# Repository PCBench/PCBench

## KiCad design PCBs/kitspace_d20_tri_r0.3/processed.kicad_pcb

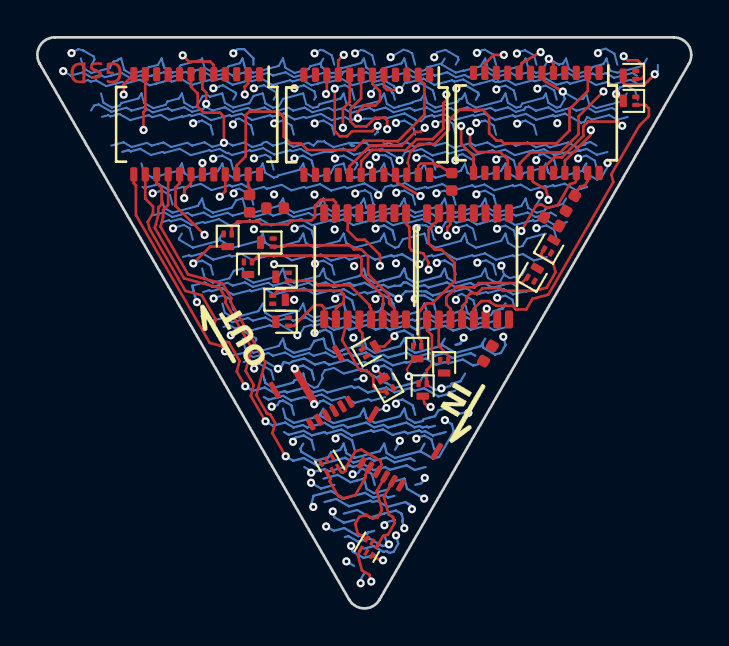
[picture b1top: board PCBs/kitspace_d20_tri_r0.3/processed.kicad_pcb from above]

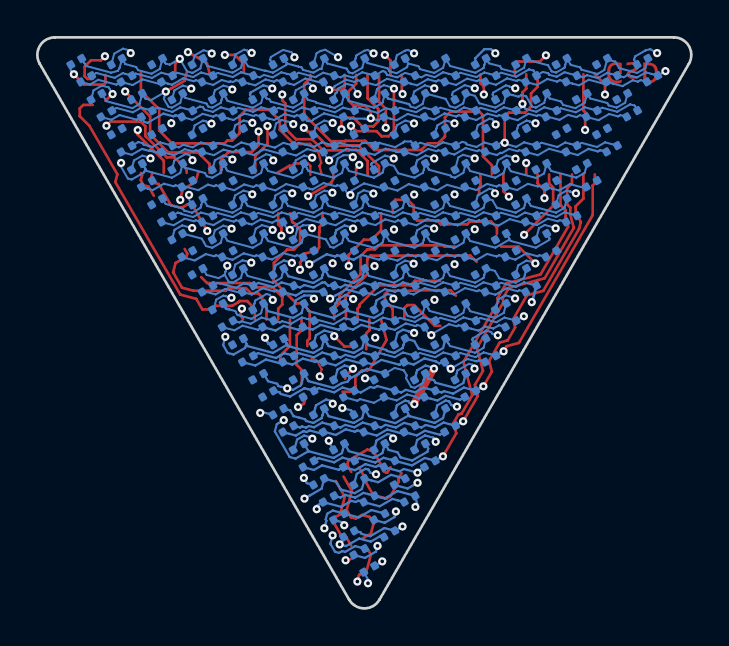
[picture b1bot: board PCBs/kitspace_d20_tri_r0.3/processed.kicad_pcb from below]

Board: 4 copper layers, 36.3 x 31.7 mm, 150 parts (120 on the bottom side), 84 nets.

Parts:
C1, C2, C3: 100nF; C_0402_1005Metric
D1, D2, D3, D4, D5, D6, D7, D8, D9, D10, D11, D12, D13, D14, D15, D17, D18, D19, D20, D21, D22, D23, D24, D25, D26, D27, D28, D29, D30, D33, D34, D35, D36, D37, D38, D39, D40, D41, D42, D43, D44, D45, D49, D50, D51, D52, D53, D54, D55, D56, D57, D58, D59, D60, D65, D66, D67, D68, D69, D70, D71, D72, D73, D74, D75, D81, D82, D83, D84, D85, D86, D87, D88, D89, D90, D97, D98, D99, D100, D101, D102, D103, D104, D105, D113, D114, D115, D116, D117, D118, D119, D120, D129, D130, D131, D132, D133, D134, D135, D145, D146, D147, D148, D149, D150, D161, D162, D163, D164, D165, D177, D178, D179, D180, D193, D194, D195, D209, D210, D225: LED_ARGB; led_rbag_1515
J1: input; 5034800600
J2: output; 5034800600
Q1, Q2, Q3, Q4, Q5, Q6, Q7, Q8, Q9, Q10, Q11, Q12, Q13, Q14, Q15: LP0404N3T5G; SOT-883
R1: 2.2k; R_0402_1005Metric
R2: 7.5k; R_0402_1005Metric
R3: 4.12k; R_0402_1005Metric
U1, U2, U3: TLC59025; SSOP-24_slim
U4, U5: 74HC595; TSSOP-16_slim
U6, U7: NC7WZ17; UDFN-6_1x1mm_P0.35mm

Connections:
U1_r_ext: R1.1, U1.23
U2_r_ext: R2.1, U2.23
U3_r_ext: R3.1, U3.23
blank: U1.21, U2.21, U3.21, U6.4
blank_i: J1.3, U6.3
colb_0: D1.2, D17.2, D33.2, D49.2, D65.2, D81.2, D97.2, D113.2, D129.2, D145.2, D161.2, D177.2, D193.2, D209.2, D225.2, U3.5
colb_1: D2.2, D18.2, D34.2, D50.2, D66.2, D82.2, D98.2, D114.2, D130.2, D146.2, D162.2, D178.2, D194.2, D210.2, U3.6
colb_3: D4.2, D20.2, D36.2, D52.2, D68.2, D84.2, D100.2, D116.2, D132.2, D148.2, D164.2, D180.2, U3.8
colb_4: D5.2, D21.2, D37.2, D53.2, D69.2, D85.2, D101.2, D117.2, D133.2, D149.2, D165.2
colb_5: D6.2, D22.2, D38.2, D54.2, D70.2, D86.2, D102.2, D118.2, D134.2, D150.2
colb_6: D7.2, D23.2, D39.2, D55.2, D71.2, D87.2, D103.2, D119.2, D135.2, U3.11
colb_7: D8.2, D24.2, D40.2, D56.2, D72.2, D88.2, D104.2, D120.2
colb_8: D9.2, D25.2, D41.2, D57.2, D73.2, D89.2, D105.2, U3.13
colb_9: D10.2, D26.2, D42.2, D58.2, D74.2, D90.2
colb_10: D11.2, D27.2, D43.2, D59.2, D75.2
colb_11: D12.2, D28.2, D44.2, D60.2, U3.16
colb_12: D13.2, D29.2, D45.2, U3.17
colb_13: D14.2, D30.2, U3.18
colb_14: D15.2, U3.19
colg_0: D1.3, D17.3, D33.3, D49.3, D65.3, D81.3, D97.3, D113.3, D129.3, D145.3, D161.3, D177.3, D193.3, D209.3, D225.3, U2.5
colg_1: D2.3, D18.3, D34.3, D50.3, D66.3, D82.3, D98.3, D114.3, D130.3, D146.3, D162.3, D178.3, D194.3, D210.3, U2.6
colg_2: D3.3, D19.3, D35.3, D51.3, D67.3, D83.3, D99.3, D115.3, D131.3, D147.3, D163.3, D179.3, D195.3, U2.7
colg_3: D4.3, D20.3, D36.3, D52.3, D68.3, D84.3, D100.3, D116.3, D132.3, D148.3, D164.3, D180.3, U2.8
colg_4: D5.3, D21.3, D37.3, D53.3, D69.3, D85.3, D101.3, D117.3, D133.3, D149.3, D165.3, U2.9
colg_5: D6.3, D22.3, D38.3, D54.3, D70.3, D86.3, D102.3, D118.3, D134.3, D150.3, U2.10
colg_6: D7.3, D23.3, D39.3, D55.3, D71.3, D103.3, D119.3, D135.3
colg_7: D8.3, D24.3, D40.3, D56.3, D72.3, D88.3, D104.3, D120.3
colg_8: D9.3, D25.3, D41.3, D57.3, D73.3, D89.3, D105.3
colg_9: D10.3, D26.3, D42.3, D58.3
colg_10: D11.3, D27.3, D43.3, D59.3, D75.3
colg_11: D12.3, D28.3, D44.3, D60.3
colg_12: D13.3, D29.3, D45.3, U2.17
colg_13: D14.3, D30.3, U2.18
colg_14: D15.3, U2.19
colr_0: D1.4, D17.4, D33.4, D49.4, D65.4, D81.4, D97.4, D113.4, D129.4, D145.4, D161.4, D177.4, D193.4, D209.4, D225.4, U1.5
colr_1: D2.4, D18.4, D34.4, D50.4, D66.4, D82.4, D98.4, D114.4, D130.4, D146.4, D162.4, D178.4, D194.4, D210.4, U1.6
colr_2: D3.4, D19.4, D35.4, D51.4, D67.4, D83.4, D99.4, D115.4, D131.4, D147.4, D163.4, D195.4, U1.7
colr_4: D5.4, D21.4, D37.4, D53.4, D69.4, D85.4, D101.4, D117.4, D133.4, D149.4, D165.4
colr_6: D7.4, D23.4, D39.4, D55.4, D71.4, D87.4, D119.4, D135.4, U1.11
colr_7: D8.4, D24.4, D40.4, D56.4, D72.4, D88.4, D104.4, D120.4, U1.12
colr_8: D9.4, D25.4, D41.4, D57.4, D73.4, D89.4, D105.4, U1.13
colr_9: D10.4, D26.4, D58.4, D74.4, D90.4, U1.14
colr_10: D11.4, D27.4, D43.4, D59.4, D75.4, U1.15
colr_11: D12.4, D28.4, D44.4, D60.4, U1.16
colr_12: D13.4, D29.4, D45.4, U1.17
colr_13: D14.4, D30.4, U1.18
colr_14: D15.4, U1.19
dat: U1.2, U6.6
dat_i: J1.2, U6.1
latch_i: J1.4, U7.3
row_0: D1.1, D5.1, D6.1, D7.1, D8.1, D9.1, D10.1, D11.1, D12.1, D13.1, D14.1, D15.1, Q1.3
row_1: D26.1, D27.1, D28.1, D29.1, D30.1
row_2: D35.1, D36.1, D37.1, D41.1, D42.1, D43.1, D44.1, D45.1
row_3: D50.1, D51.1, D52.1, D54.1, D55.1, D56.1, D58.1, D59.1, D60.1, Q4.3
row_4: D65.1, D66.1, D67.1, D68.1, D72.1, D73.1, D75.1, Q5.3
row_5: D82.1, D83.1, D84.1, D85.1, D86.1, D88.1, D89.1
row_6: D97.1, D98.1, D99.1, D100.1, D101.1, D102.1, D103.1, D104.1
row_7: D113.1, D114.1, D115.1, D116.1, D117.1, D118.1, D119.1, D120.1
row_8: D129.1, D130.1, D131.1, D132.1, D133.1, D134.1, Q9.3
row_9: D145.1, D146.1, D147.1, D148.1, D149.1, D150.1, Q10.3
row_10: D161.1, D162.1, D163.1, D164.1
row_11: D177.1, D178.1, D180.1
row_13: D209.1, D210.1, Q14.3
row_14: D225.1, Q15.3
sclk_i: J1.5, U7.1
sdo_U1>sdi_U2: U1.22, U2.2
sdo_U2>sdi_U3: U2.22, U3.2
sdo_U3: U3.22, U4.14
sdo_U4>sdi_U5: U4.9, U5.14
srow_0: Q1.1, U4.15
srow_1: Q2.1, U4.1
srow_2: Q3.1, U4.2
srow_3: Q4.1, U4.3
srow_4: Q5.1, U4.4
srow_5: Q6.1, U4.5
srow_6: Q7.1, U4.6
srow_7: Q8.1, U4.7
srow_8: Q9.1, U5.15
srow_9: Q10.1, U5.1
srow_10: Q11.1, U5.2
srow_11: Q12.1, U5.3
srow_12: Q13.1, U5.4
srow_13: Q14.1, U5.5
srow_14: Q15.1, U5.6

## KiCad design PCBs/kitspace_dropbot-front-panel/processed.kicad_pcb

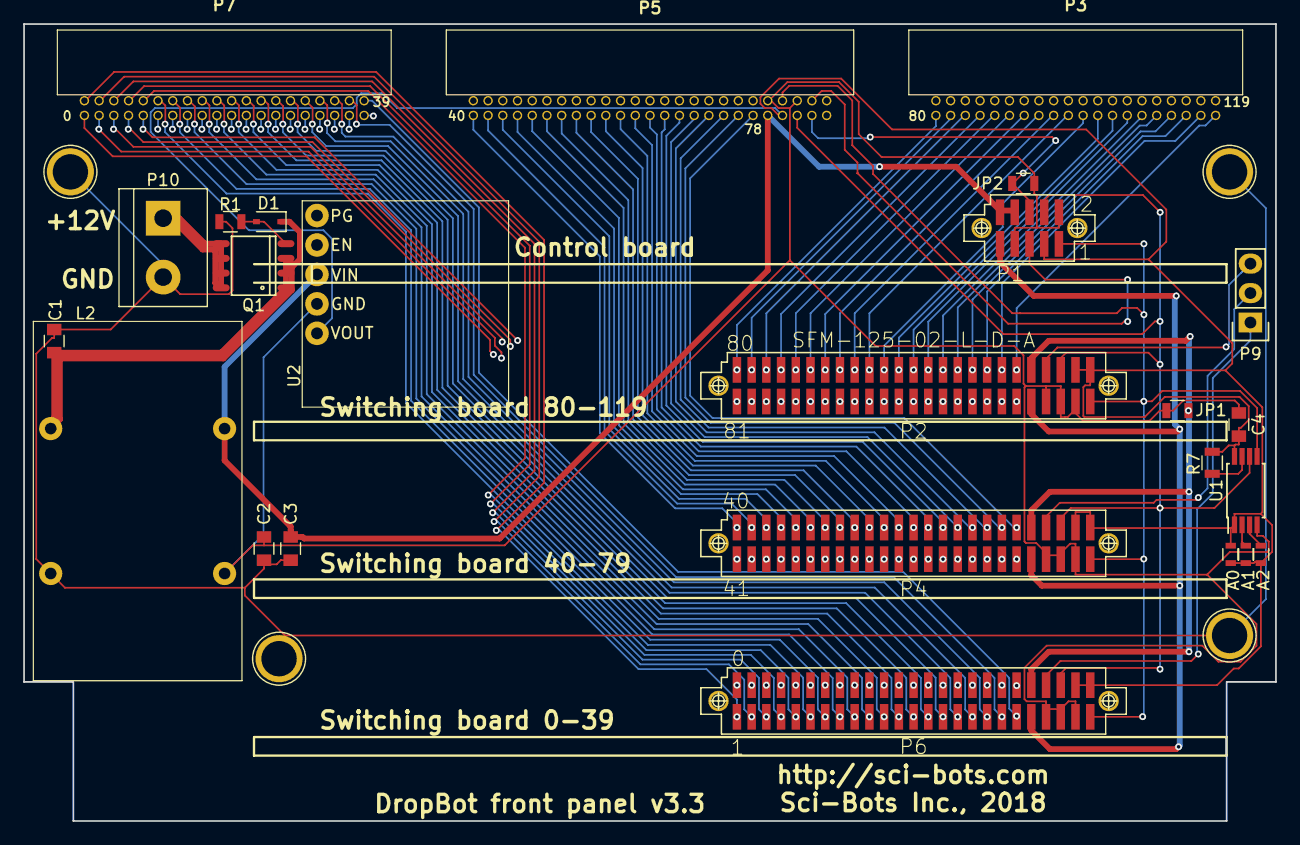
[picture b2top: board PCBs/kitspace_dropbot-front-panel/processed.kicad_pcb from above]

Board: 4 copper layers, 108.0 x 68.8 mm, 29 parts (0 on the bottom side), 139 nets.

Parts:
C1, C2, C3, C4: 0.1uF; C_0805
D1: 10V; D_SOD-323
JP1, JP2: JUMPER; R_0805
JP3: A0; R_0603
JP4: A1; R_0603
JP5: A2; R_0603
L2: 1.8mH; RN242-X-02-XXX
P1: SFM-105-02-L-D-A; SFM-105-02-XXX-D-A
P2, P4, P6: SFM-125-02-L-D-A; SFM-125-02-XXX-D-A
P3, P7: TFM-120-01-L-D-RA; TFM-120-01-XXX-D-RA
P5: TFM-125-01-L-D-RA; TFM-125-01-XXX-D-RA
P8, P13, P14, P15: Conn_01x01; 1pin
P9: Conn_01x03; Pin_Header_Straight_1x03
P10: Conn_01x02; bornier2
Q1: IRF9388TRPBF; SO-8
R1, R7: 10k; R_0805
U1: CAT24C__; TSSOP-8_4.4x3mm_Pitch0.65mm
U2: D24V22F3; D24V22F

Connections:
+3.3V: C4.1, JP3.1, JP3.2, JP4.1, JP5.1, P1.3, P2.2, P2.4, P4.2, P4.4, P5.8, P6.2, P6.4, R7.1, U1.1, U1.8, U2.5
+12V: C3.1, L2.2, P1.8, P1.10, P5.10, U2.3
/+12V_SUPPLY: P10.1, Q1.5, Q1.6, Q1.7, Q1.8
CHASIS_GND: C1.2, C2.2, C3.2, L2.4, P8.1, P10.2, P13.1, P14.1, P15.1, R1.2
CUR_SENSE: P1.5, P5.3
GND: C2.1, C4.2, JP1.1, JP2.1, L2.3, P1.2, P1.7, P2.3, P2.5, P2.7, P4.3, P4.5, P4.7, P5.5, P5.9, P6.3, P6.5, P6.7, U1.4, U2.4
HVAC: P1.9, P2.9, P4.9, P6.9
HVGND: JP1.2, P2.10, P4.10, P6.10
HVOUT0: P6.50, P7.40
HVOUT1: P6.49, P7.39
HVOUT2: P6.48, P7.38
HVOUT3: P6.47, P7.37
HVOUT4: P6.46, P7.36
HVOUT5: P6.45, P7.35
HVOUT6: P6.44, P7.34
HVOUT7: P6.43, P7.33
HVOUT8: P6.42, P7.32
HVOUT9: P6.41, P7.31
HVOUT10: P6.40, P7.30
HVOUT11: P6.39, P7.29
HVOUT12: P6.38, P7.28
HVOUT13: P6.37, P7.27
HVOUT14: P6.36, P7.26
HVOUT15: P6.35, P7.25
HVOUT16: P6.34, P7.24
HVOUT17: P6.33, P7.23
HVOUT18: P6.32, P7.22
HVOUT19: P6.31, P7.21
HVOUT20: P6.30, P7.20
HVOUT21: P6.29, P7.19
HVOUT22: P6.28, P7.18
HVOUT23: P6.27, P7.17
HVOUT24: P6.26, P7.16
HVOUT25: P6.25, P7.15
HVOUT26: P6.24, P7.14
HVOUT27: P6.23, P7.13
HVOUT28: P6.22, P7.12
HVOUT29: P6.21, P7.11
HVOUT30: P6.20, P7.10
HVOUT31: P6.19, P7.9
HVOUT32: P6.18, P7.8
HVOUT33: P6.17, P7.7
HVOUT34: P6.16, P7.6
HVOUT35: P6.15, P7.5
HVOUT36: P6.14, P7.4
HVOUT37: P6.13, P7.3
HVOUT38: P6.12, P7.2
HVOUT39: P6.11, P7.1
HVOUT40: P4.50, P5.50
HVOUT41: P4.49, P5.49
HVOUT42: P4.48, P5.48
HVOUT43: P4.47, P5.47
HVOUT44: P4.46, P5.46
HVOUT45: P4.45, P5.45
HVOUT46: P4.44, P5.44
HVOUT47: P4.43, P5.43
HVOUT48: P4.42, P5.42
HVOUT49: P4.41, P5.41
HVOUT50: P4.40, P5.40
HVOUT51: P4.39, P5.39
HVOUT52: P4.38, P5.38
HVOUT53: P4.37, P5.37
HVOUT54: P4.36, P5.36
HVOUT55: P4.35, P5.35
HVOUT56: P4.34, P5.34
HVOUT57: P4.33, P5.33
HVOUT58: P4.32, P5.32
HVOUT59: P4.31, P5.31
HVOUT60: P4.30, P5.30
HVOUT61: P4.29, P5.29
HVOUT62: P4.28, P5.28
HVOUT63: P4.27, P5.27
HVOUT64: P4.26, P5.26
HVOUT65: P4.25, P5.25
HVOUT66: P4.24, P5.24
HVOUT67: P4.23, P5.23
HVOUT68: P4.22, P5.22
HVOUT69: P4.21, P5.21
HVOUT70: P4.20, P5.20
HVOUT71: P4.19, P5.19
HVOUT72: P4.18, P5.18
HVOUT73: P4.17, P5.17
HVOUT74: P4.16, P5.16
HVOUT75: P4.15, P5.15
HVOUT76: P4.14, P5.14
HVOUT77: P4.13, P5.13
HVOUT78: P4.12, P5.12
HVOUT79: P4.11, P5.11
HVOUT80: P2.50, P3.40
HVOUT81: P2.49, P3.39
HVOUT82: P2.48, P3.38
HVOUT83: P2.47, P3.37
HVOUT84: P2.46, P3.36
HVOUT85: P2.45, P3.35
HVOUT86: P2.44, P3.34
HVOUT87: P2.43, P3.33
HVOUT88: P2.42, P3.32
HVOUT89: P2.41, P3.31
HVOUT90: P2.40, P3.30
HVOUT91: P2.39, P3.29
HVOUT92: P2.38, P3.28
HVOUT93: P2.37, P3.27
HVOUT94: P2.36, P3.26
HVOUT95: P2.35, P3.25
HVOUT96: P2.34, P3.24
HVOUT97: P2.33, P3.23
HVOUT98: P2.32, P3.22
HVOUT99: P2.31, P3.21
HVOUT100: P2.30, P3.20
HVOUT101: P2.29, P3.19
HVOUT102: P2.28, P3.18
HVOUT103: P2.27, P3.17
HVOUT104: P2.26, P3.16
HVOUT105: P2.25, P3.15
HVOUT106: P2.24, P3.14
HVOUT107: P2.23, P3.13
HVOUT108: P2.22, P3.12
HVOUT109: P2.21, P3.11
HVOUT110: P2.20, P3.10
HVOUT111: P2.19, P3.9
HVOUT112: P2.18, P3.8
HVOUT113: P2.17, P3.7
HVOUT114: P2.16, P3.6
HVOUT115: P2.15, P3.5
HVOUT116: P2.14, P3.4
HVOUT117: P2.13, P3.3
HVOUT118: P2.12, P3.2
HVOUT119: P2.11, P3.1
HV_OE: JP2.2, P1.6, P5.4
unnamed: C1.1, D1.1, L2.1, Q1.1, Q1.2, Q1.3
unnamed: D1.2, Q1.4, R1.1
unnamed: JP4.2, U1.2
unnamed: JP5.2, U1.3
unnamed: R7.2, U1.7
RST1: P6.8, P9.1
RST2: P4.8, P9.2
RST3: P2.8, P9.3
SCL: P1.4, P2.6, P4.6, P5.6, P6.6, U1.6
SDA: P1.1, P2.1, P4.1, P5.7, P6.1, U1.5
